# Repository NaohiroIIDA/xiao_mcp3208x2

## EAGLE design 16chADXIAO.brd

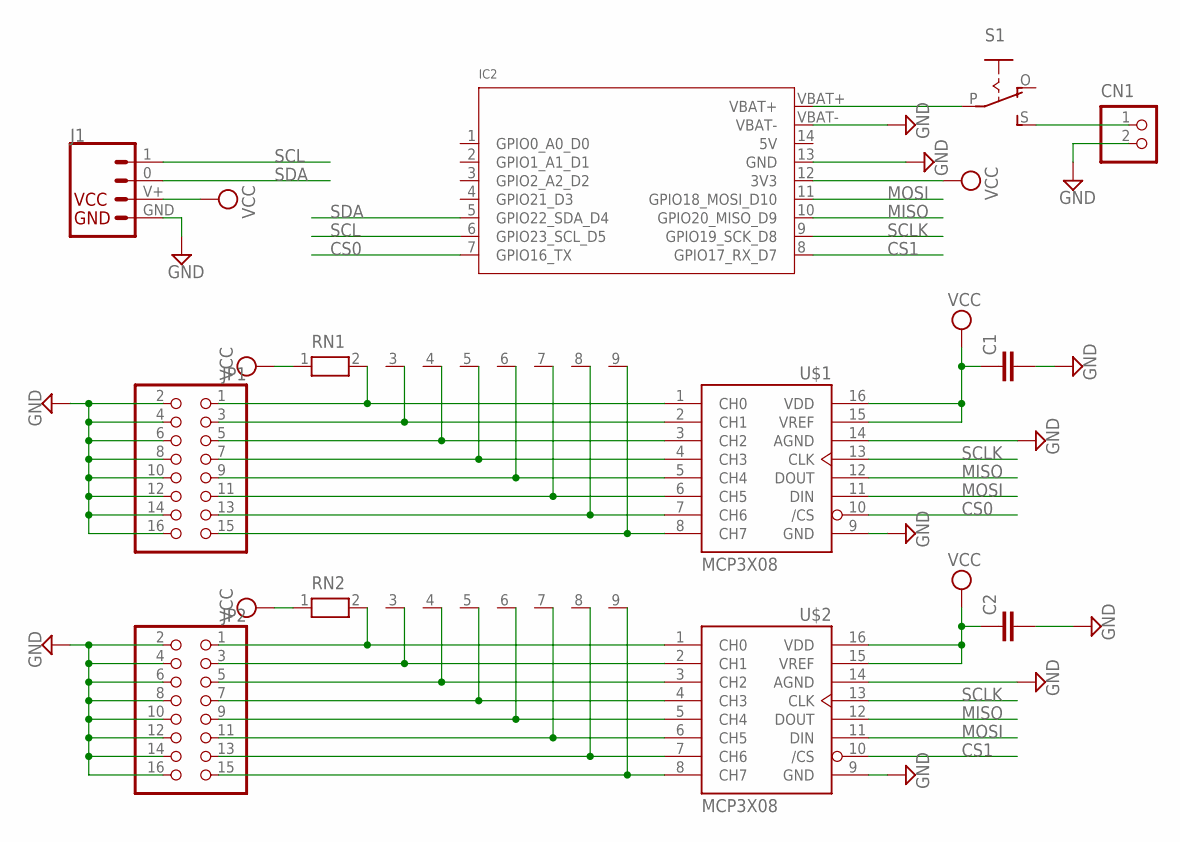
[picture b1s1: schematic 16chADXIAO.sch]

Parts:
C1, C2: C-EUC0805; C0805
CN1: B2B-PH-K-S
IC2: MOUDLE-XIAO-ESO32C6; XIAO-ESP32C6
J1: 4P-2.0; HW4-2.0-90D
JP1, JP2: PINHD-2X8/90; 2X08/90
RN1, RN2: RN08; RN-9
S1: EG1218S; EG1218
U$1, U$2: MCP3X08; SO16

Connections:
CS0: IC2.7 (GPIO16_TX), U$1.10 (/CS)
CS1: IC2.8 (GPIO17_RX_D7), U$2.10 (/CS)
GND: C1.2, C2.2, CN1.2, IC2.13 (GND), IC2.VBAT-, J1.GND, JP1.2, JP1.4, JP1.6, JP1.8, JP1.10, JP1.12, JP1.14, JP1.16, JP2.2, JP2.4, JP2.6, JP2.8, JP2.10, JP2.12, JP2.14, JP2.16, U$1.9 (GND), U$1.14 (AGND), U$2.9 (GND), U$2.14 (AGND)
MISO: IC2.10 (GPIO20_MISO_D9), U$1.12 (DOUT), U$2.12 (DOUT)
MOSI: IC2.11 (GPIO18_MOSI_D10), U$1.11 (DIN), U$2.11 (DIN)
unnamed: JP1.1, RN1.2, U$1.1 (CH0)
unnamed: JP1.3, RN1.3, U$1.2 (CH1)
unnamed: JP1.5, RN1.4, U$1.3 (CH2)
unnamed: JP1.7, RN1.5, U$1.4 (CH3)
unnamed: JP1.9, RN1.6, U$1.5 (CH4)
unnamed: JP1.11, RN1.7, U$1.6 (CH5)
unnamed: JP1.13, RN1.8, U$1.7 (CH6)
unnamed: JP1.15, RN1.9, U$1.8 (CH7)
unnamed: JP2.1, RN2.2, U$2.1 (CH0)
unnamed: JP2.3, RN2.3, U$2.2 (CH1)
unnamed: JP2.5, RN2.4, U$2.3 (CH2)
unnamed: JP2.7, RN2.5, U$2.4 (CH3)
unnamed: JP2.9, RN2.6, U$2.5 (CH4)
unnamed: JP2.11, RN2.7, U$2.6 (CH5)
unnamed: JP2.13, RN2.8, U$2.7 (CH6)
unnamed: JP2.15, RN2.9, U$2.8 (CH7)
unnamed: IC2.VBAT+, S1.P
unnamed: CN1.1, S1.S
SCL: IC2.6 (GPIO23_SCL_D5), J1.1 (4)
SCLK: IC2.9 (GPIO19_SCK_D8), U$1.13 (CLK), U$2.13 (CLK)
SDA: IC2.5 (GPIO22_SDA_D4), J1.0 (3)
VCC: C1.1, C2.1, IC2.12 (3V3), J1.V+ (VCC), RN1.1, RN2.1, U$1.15 (VREF), U$1.16 (VDD), U$2.15 (VREF), U$2.16 (VDD)

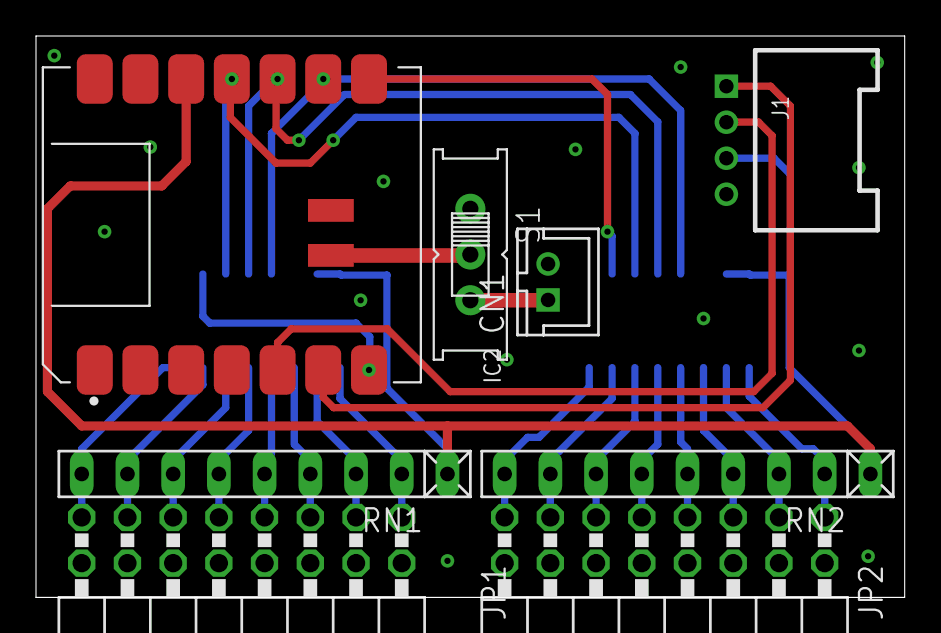
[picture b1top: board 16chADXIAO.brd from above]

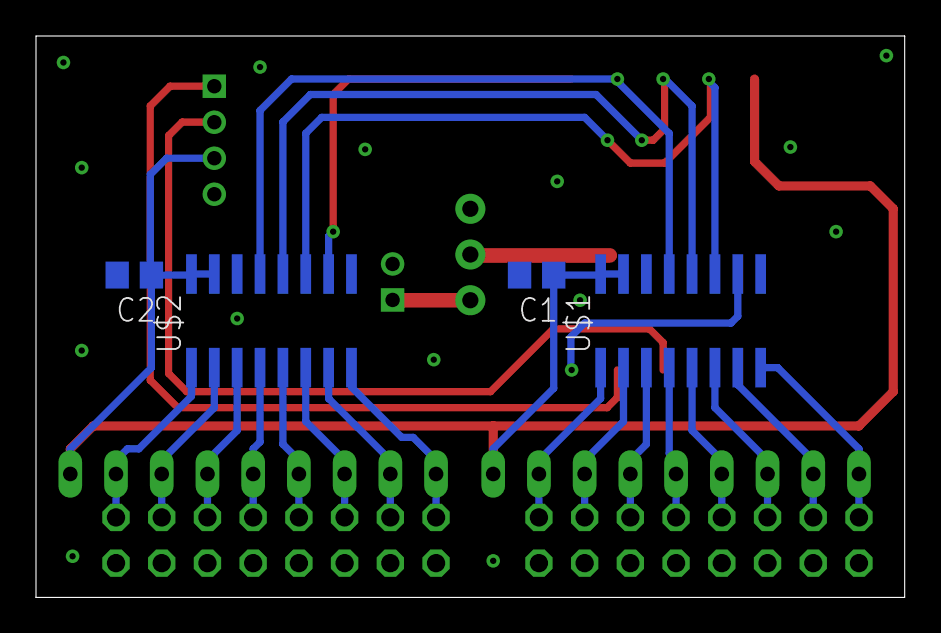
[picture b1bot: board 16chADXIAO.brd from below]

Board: 2 copper layers, 48.3 x 31.2 mm, 12 parts (4 on the bottom side), 27 nets.
